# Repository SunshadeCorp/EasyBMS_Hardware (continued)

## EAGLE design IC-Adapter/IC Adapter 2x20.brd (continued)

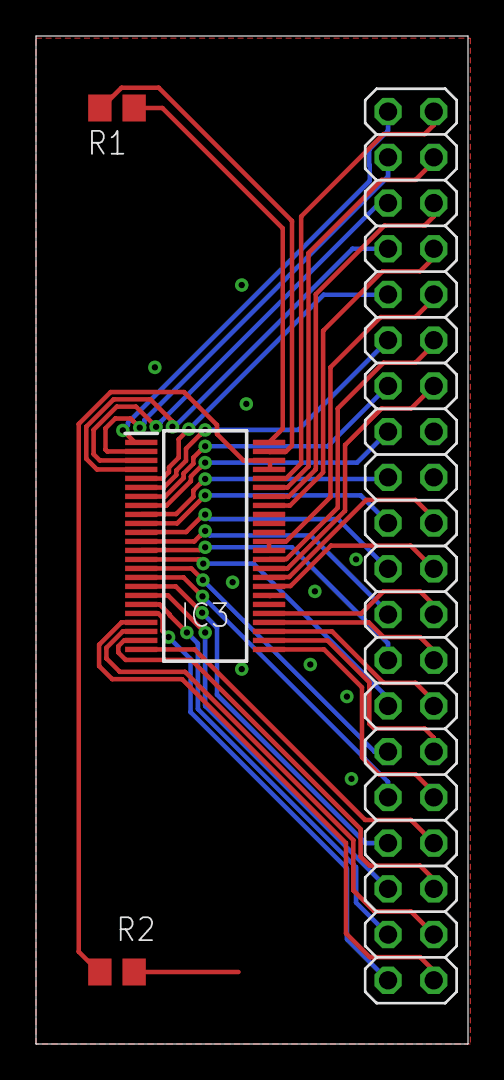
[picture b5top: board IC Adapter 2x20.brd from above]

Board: 2 copper layers, 24.0 x 56.0 mm, 4 parts (0 on the bottom side), 42 nets.

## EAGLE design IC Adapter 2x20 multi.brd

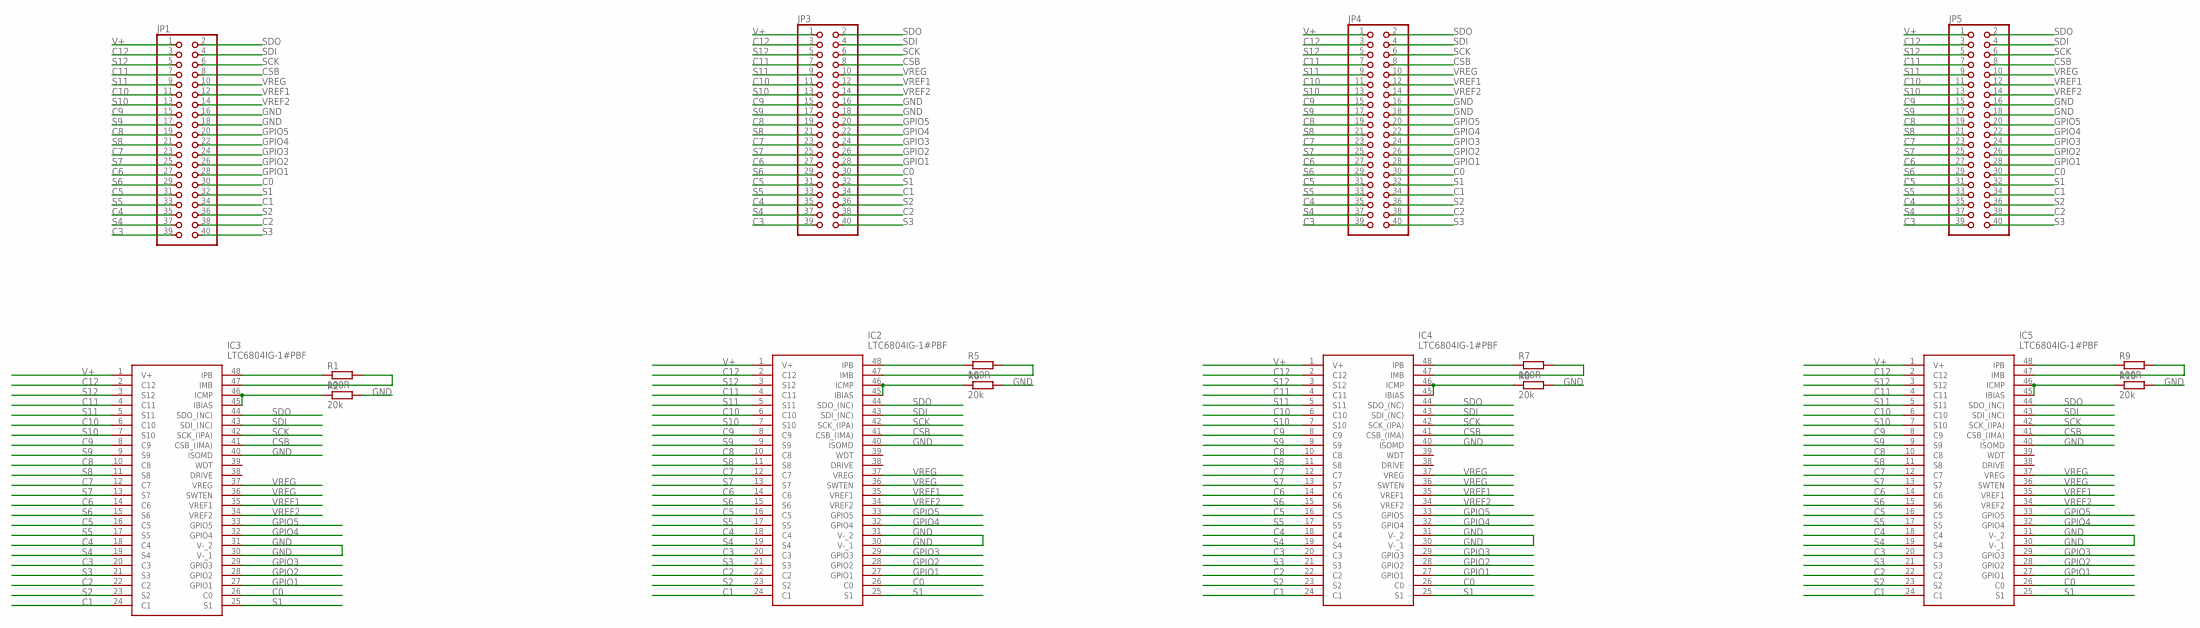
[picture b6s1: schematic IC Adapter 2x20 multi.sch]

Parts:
IC2, IC3, IC4, IC5: LTC6804IG-1#PBF; SOP50P780X200-48N
JP1, JP3, JP4, JP5: PINHD-2X20; 2X20
R1, R5, R7, R9: 100R; R0805
R2, R6, R8, R10: 20k; R0805

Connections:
C0: IC2.26 (C0), IC3.26 (C0), IC4.26 (C0), IC5.26 (C0), JP1.30, JP3.30, JP4.30, JP5.30
C1: IC2.24 (C1), IC3.24 (C1), IC4.24 (C1), IC5.24 (C1), JP1.34, JP3.34, JP4.34, JP5.34
C2: IC2.22 (C2), IC3.22 (C2), IC4.22 (C2), IC5.22 (C2), JP1.38, JP3.38, JP4.38, JP5.38
C3: IC2.20 (C3), IC3.20 (C3), IC4.20 (C3), IC5.20 (C3), JP1.39, JP3.39, JP4.39, JP5.39
C4: IC2.18 (C4), IC3.18 (C4), IC4.18 (C4), IC5.18 (C4), JP1.35, JP3.35, JP4.35, JP5.35
C5: IC2.16 (C5), IC3.16 (C5), IC4.16 (C5), IC5.16 (C5), JP1.31, JP3.31, JP4.31, JP5.31
C6: IC2.14 (C6), IC3.14 (C6), IC4.14 (C6), IC5.14 (C6), JP1.27, JP3.27, JP4.27, JP5.27
C7: IC2.12 (C7), IC3.12 (C7), IC4.12 (C7), IC5.12 (C7), JP1.23, JP3.23, JP4.23, JP5.23
C8: IC2.10 (C8), IC3.10 (C8), IC4.10 (C8), IC5.10 (C8), JP1.19, JP3.19, JP4.19, JP5.19
C9: IC2.8 (C9), IC3.8 (C9), IC4.8 (C9), IC5.8 (C9), JP1.15, JP3.15, JP4.15, JP5.15
C10: IC2.6 (C10), IC3.6 (C10), IC4.6 (C10), IC5.6 (C10), JP1.11, JP3.11, JP4.11, JP5.11
C11: IC2.4 (C11), IC3.4 (C11), IC4.4 (C11), IC5.4 (C11), JP1.7, JP3.7, JP4.7, JP5.7
C12: IC2.2 (C12), IC3.2 (C12), IC4.2 (C12), IC5.2 (C12), JP1.3, JP3.3, JP4.3, JP5.3
CSB: IC2.41 (CSB_(IMA)), IC3.41 (CSB_(IMA)), IC4.41 (CSB_(IMA)), IC5.41 (CSB_(IMA)), JP1.8, JP3.8, JP4.8, JP5.8
GND: IC2.30 (V-_1), IC2.31 (V-_2), IC2.40 (ISOMD), IC3.30 (V-_1), IC3.31 (V-_2), IC3.40 (ISOMD), IC4.30 (V-_1), IC4.31 (V-_2), IC4.40 (ISOMD), IC5.30 (V-_1), IC5.31 (V-_2), IC5.40 (ISOMD), JP1.16, JP1.18, JP3.16, JP3.18, JP4.16, JP4.18, JP5.16, JP5.18, R2.2, R6.2, R8.2, R10.2
GPIO1: IC2.27 (GPIO1), IC3.27 (GPIO1), IC4.27 (GPIO1), IC5.27 (GPIO1), JP1.28, JP3.28, JP4.28, JP5.28
GPIO2: IC2.28 (GPIO2), IC3.28 (GPIO2), IC4.28 (GPIO2), IC5.28 (GPIO2), JP1.26, JP3.26, JP4.26, JP5.26
GPIO3: IC2.29 (GPIO3), IC3.29 (GPIO3), IC4.29 (GPIO3), IC5.29 (GPIO3), JP1.24, JP3.24, JP4.24, JP5.24
GPIO4: IC2.32 (GPIO4), IC3.32 (GPIO4), IC4.32 (GPIO4), IC5.32 (GPIO4), JP1.22, JP3.22, JP4.22, JP5.22
GPIO5: IC2.33 (GPIO5), IC3.33 (GPIO5), IC4.33 (GPIO5), IC5.33 (GPIO5), JP1.20, JP3.20, JP4.20, JP5.20
ICMP: IC3.45 (IBIAS), IC3.46 (ICMP), R2.1
ICMP2: IC2.45 (IBIAS), IC2.46 (ICMP), R6.1
ICMP3: IC4.45 (IBIAS), IC4.46 (ICMP), R8.1
ICMP4: IC5.45 (IBIAS), IC5.46 (ICMP), R10.1
unnamed: IC3.48 (IPB), R1.1
unnamed: IC3.47 (IMB), R1.2
unnamed: IC2.48 (IPB), R5.1
unnamed: IC2.47 (IMB), R5.2
unnamed: IC4.48 (IPB), R7.1
unnamed: IC4.47 (IMB), R7.2
unnamed: IC5.48 (IPB), R9.1
unnamed: IC5.47 (IMB), R9.2
S1: IC2.25 (S1), IC3.25 (S1), IC4.25 (S1), IC5.25 (S1), JP1.32, JP3.32, JP4.32, JP5.32
S2: IC2.23 (S2), IC3.23 (S2), IC4.23 (S2), IC5.23 (S2), JP1.36, JP3.36, JP4.36, JP5.36
S3: IC2.21 (S3), IC3.21 (S3), IC4.21 (S3), IC5.21 (S3), JP1.40, JP3.40, JP4.40, JP5.40
S4: IC2.19 (S4), IC3.19 (S4), IC4.19 (S4), IC5.19 (S4), JP1.37, JP3.37, JP4.37, JP5.37
S5: IC2.17 (S5), IC3.17 (S5), IC4.17 (S5), IC5.17 (S5), JP1.33, JP3.33, JP4.33, JP5.33
S6: IC2.15 (S6), IC3.15 (S6), IC4.15 (S6), IC5.15 (S6), JP1.29, JP3.29, JP4.29, JP5.29
S7: IC2.13 (S7), IC3.13 (S7), IC4.13 (S7), IC5.13 (S7), JP1.25, JP3.25, JP4.25, JP5.25
S8: IC2.11 (S8), IC3.11 (S8), IC4.11 (S8), IC5.11 (S8), JP1.21, JP3.21, JP4.21, JP5.21
S9: IC2.9 (S9), IC3.9 (S9), IC4.9 (S9), IC5.9 (S9), JP1.17, JP3.17, JP4.17, JP5.17
S10: IC2.7 (S10), IC3.7 (S10), IC4.7 (S10), IC5.7 (S10), JP1.13, JP3.13, JP4.13, JP5.13
S11: IC2.5 (S11), IC3.5 (S11), IC4.5 (S11), IC5.5 (S11), JP1.9, JP3.9, JP4.9, JP5.9
S12: IC2.3 (S12), IC3.3 (S12), IC4.3 (S12), IC5.3 (S12), JP1.5, JP3.5, JP4.5, JP5.5
SCK: IC2.42 (SCK_(IPA)), IC3.42 (SCK_(IPA)), IC4.42 (SCK_(IPA)), IC5.42 (SCK_(IPA)), JP1.6, JP3.6, JP4.6, JP5.6
SDI: IC2.43 (SDI_(NC)), IC3.43 (SDI_(NC)), IC4.43 (SDI_(NC)), IC5.43 (SDI_(NC)), JP1.4, JP3.4, JP4.4, JP5.4
SDO: IC2.44 (SDO_(NC)), IC3.44 (SDO_(NC)), IC4.44 (SDO_(NC)), IC5.44 (SDO_(NC)), JP1.2, JP3.2, JP4.2, JP5.2
V+: IC2.1 (V+), IC3.1 (V+), IC4.1 (V+), IC5.1 (V+), JP1.1, JP3.1, JP4.1, JP5.1
VREF1: IC2.35 (VREF1), IC3.35 (VREF1), IC4.35 (VREF1), IC5.35 (VREF1), JP1.12, JP3.12, JP4.12, JP5.12
VREF2: IC2.34 (VREF2), IC3.34 (VREF2), IC4.34 (VREF2), IC5.34 (VREF2), JP1.14, JP3.14, JP4.14, JP5.14
VREG: IC2.36 (SWTEN), IC2.37 (VREG), IC3.36 (SWTEN), IC3.37 (VREG), IC4.36 (SWTEN), IC4.37 (VREG), IC5.36 (SWTEN), IC5.37 (VREG), JP1.10, JP3.10, JP4.10, JP5.10

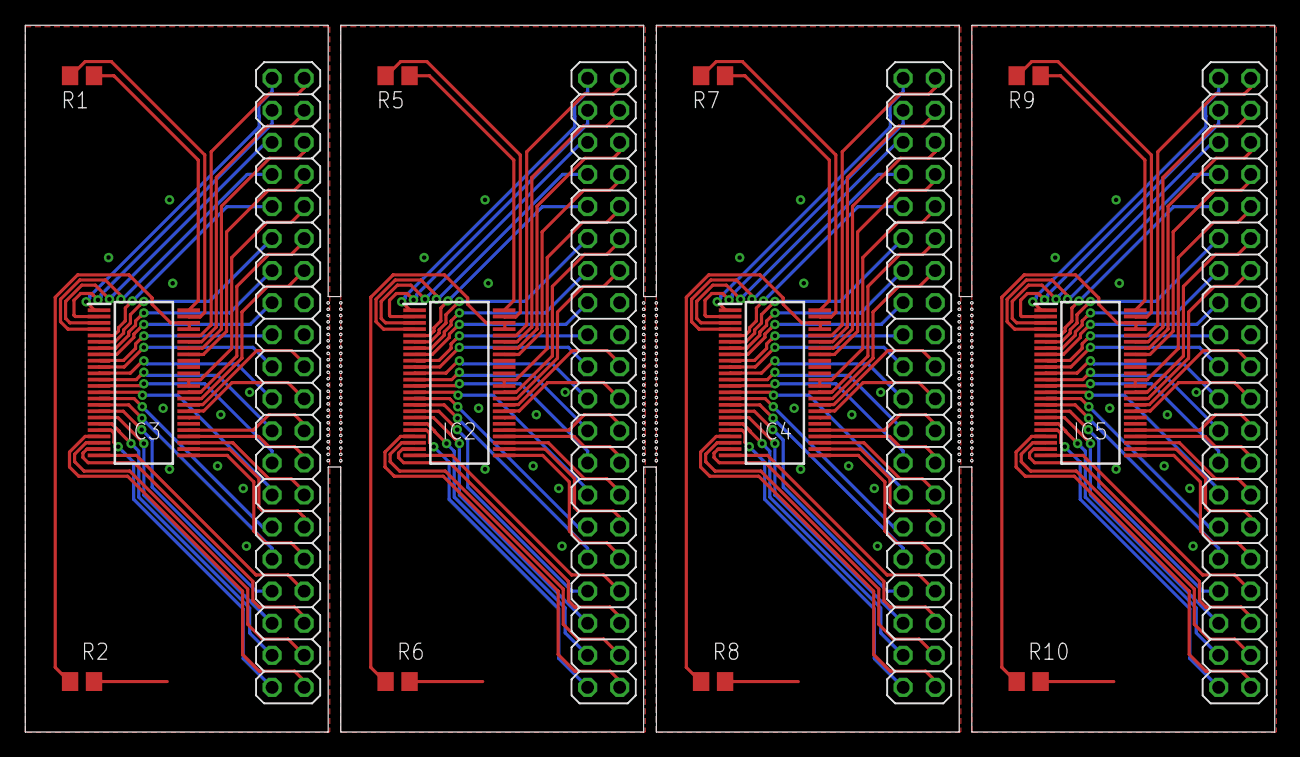
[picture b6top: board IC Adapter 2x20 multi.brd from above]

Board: 2 copper layers, 99.0 x 56.0 mm, 16 parts (0 on the bottom side), 51 nets.

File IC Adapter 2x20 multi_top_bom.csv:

Comment,Designator,Footprint,LCSC Part #
20k,R2 R6 R8,R0805,
100R,R1 R5 R7,R0805,
LTC6804IG-1#PBF,IC2 IC3 IC4,SOP50P780X200-48N,

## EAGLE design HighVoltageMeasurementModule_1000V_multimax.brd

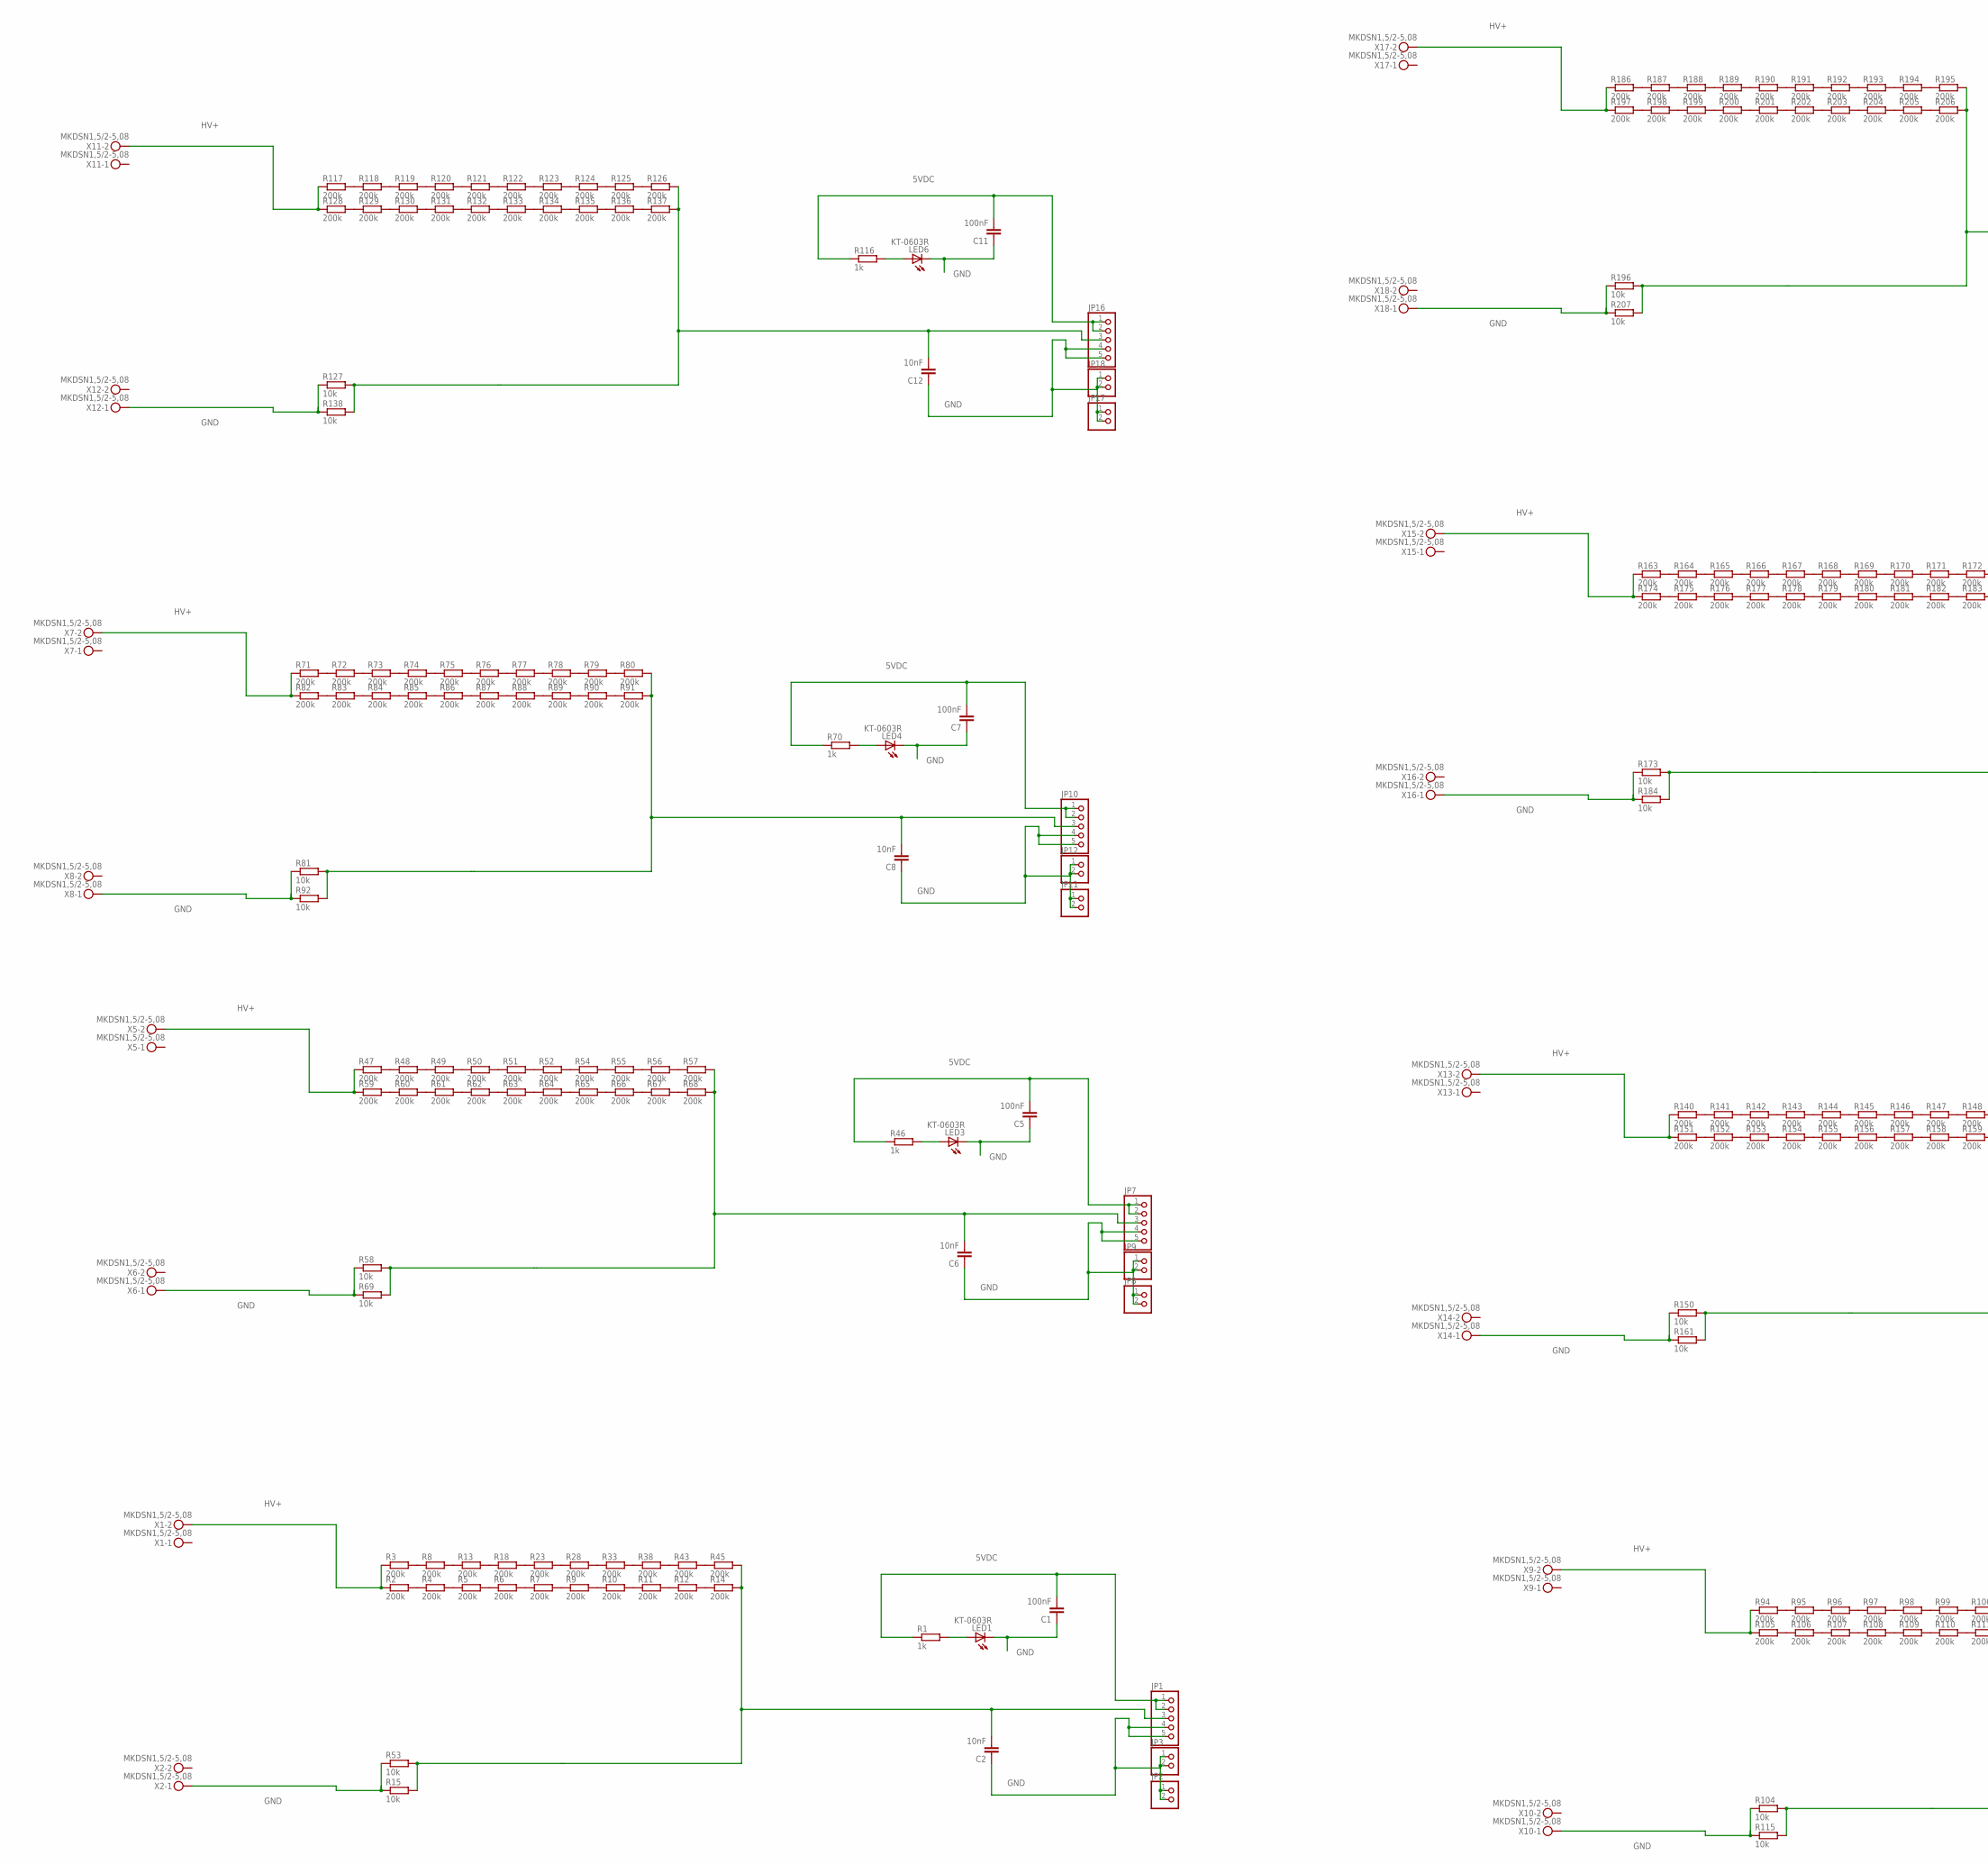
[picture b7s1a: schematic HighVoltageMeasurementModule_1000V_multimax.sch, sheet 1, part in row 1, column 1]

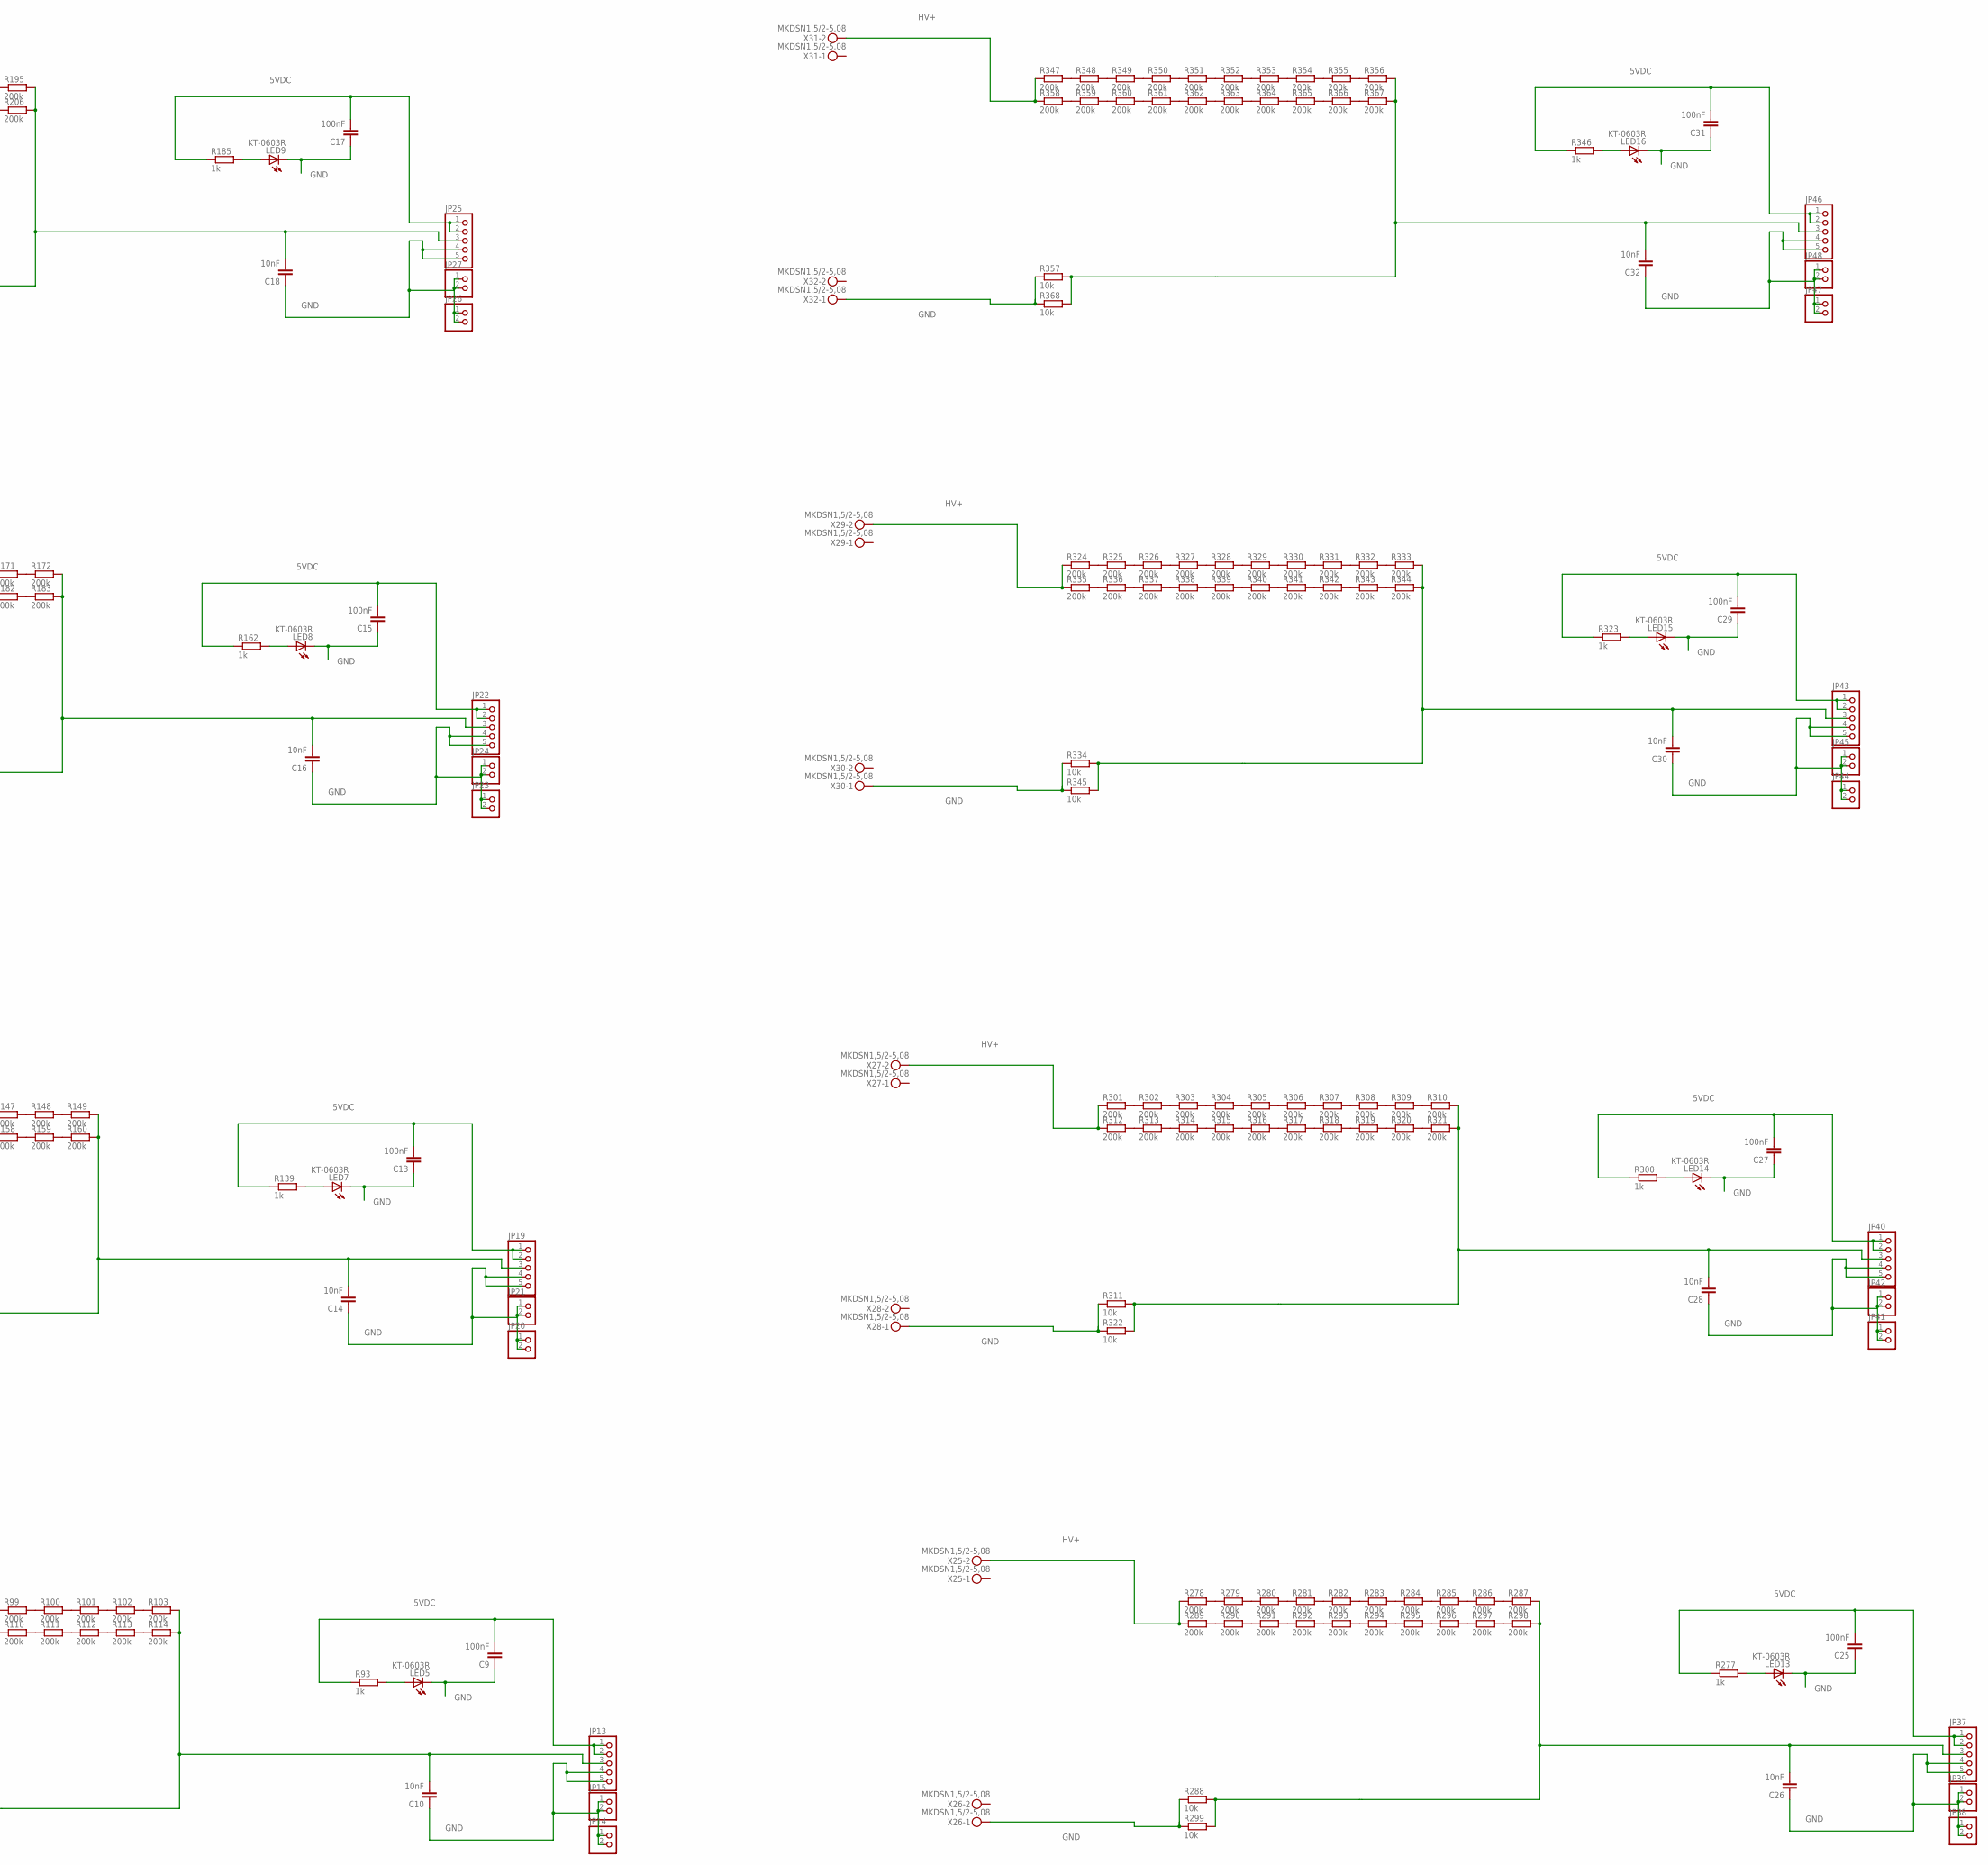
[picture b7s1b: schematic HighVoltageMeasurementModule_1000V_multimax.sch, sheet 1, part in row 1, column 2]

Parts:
C1, C5, C7, C9, C11, C13, C15, C17, C25, C27, C29, C31: 100nF; C0805
C2, C6, C8, C10, C12, C14, C16, C18, C26, C28, C30, C32: 10nF; C0805
JP1, JP7, JP10, JP13, JP16, JP19, JP22, JP25, JP37, JP40, JP43, JP46: PINHD-1X5; 1X05
JP2, JP3, JP8, JP9, JP11, JP12, JP14, JP15, JP17, JP18, JP20, JP21, JP23, JP24, JP26, JP27, JP38, JP39, JP41, JP42, JP44, JP45, JP47, JP48: PINHD-1X2; 1X02
LED1, LED3, LED4, LED5, LED6, LED7, LED8, LED9, LED13, LED14, LED15, LED16: KT-0603R; CHIPLED_0603
R1, R46, R70, R93, R116, R139, R162, R185, R277, R300, R323, R346: 1k; R0805
R2, R3, R4, R5, R6, R7, R8, R9, R10, R11, R12, R13, R14, R18, R23, R28, R33, R38, R43, R45, R47, R48, R49, R50, R51, R52, R54, R55, R56, R57, R59, R60, R61, R62, R63, R64, R65, R66, R67, R68, R71, R72, R73, R74, R75, R76, R77, R78, R79, R80, R82, R83, R84, R85, R86, R87, R88, R89, R90, R91, R94, R95, R96, R97, R98, R99, R100, R101, R102, R103, R105, R106, R107, R108, R109, R110, R111, R112, R113, R114, R117, R118, R119, R120, R121, R122, R123, R124, R125, R126, R128, R129, R130, R131, R132, R133, R134, R135, R136, R137, R140, R141, R142, R143, R144, R145, R146, R147, R148, R149, R151, R152, R153, R154, R155, R156, R157, R158, R159, R160, R163, R164, R165, R166, R167, R168, R169, R170, R171, R172, R174, R175, R176, R177, R178, R179, R180, R181, R182, R183, R186, R187, R188, R189, R190, R191, R192, R193, R194, R195, R197, R198, R199, R200, R201, R202, R203, R204, R205, R206, R278, R279, R280, R281, R282, R283, R284, R285, R286, R287, R289, R290, R291, R292, R293, R294, R295, R296, R297, R298, R301, R302, R303, R304, R305, R306, R307, R308, R309, R310, R312, R313, R314, R315, R316, R317, R318, R319, R320, R321, R324, R325, R326, R327, R328, R329, R330, R331, R332, R333, R335, R336, R337, R338, R339, R340, R341, R342, R343, R344, R347, R348, R349, R350, R351, R352, R353, R354, R355, R356, R358, R359, R360, R361, R362, R363, R364, R365, R366, R367: 200k; R0805
R15, R53, R58, R69, R81, R92, R104, R115, R127, R138, R150, R161, R173, R184, R196, R207, R288, R299, R311, R322, R334, R345, R357, R368: 10k; R0805
X1, X2, X5, X6, X7, X8, X9, X10, X11, X12, X13, X14, X15, X16, X17, X18, X25, X26, X27, X28, X29, X30, X31, X32: MKDSN1,5/2-5,08

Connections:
5VDC: C1.2, C5.2, C7.2, C9.2, C11.2, C13.2, C15.2, C17.2, C25.2, C27.2, C29.2, C31.2, JP1.1, JP1.2, JP7.1, JP7.2, JP10.1, JP10.2, JP13.1, JP13.2, JP16.1, JP16.2, JP19.1, JP19.2, JP22.1, JP22.2, JP25.1, JP25.2, JP37.1, JP37.2, JP40.1, JP40.2, JP43.1, JP43.2, JP46.1, JP46.2, R1.1, R46.1, R70.1, R93.1, R116.1, R139.1, R162.1, R185.1, R277.1, R300.1, R323.1, R346.1
GND: C1.1, C2.1, C5.1, C6.1, C7.1, C8.1, C9.1, C10.1, C11.1, C12.1, C13.1, C14.1, C15.1, C16.1, C17.1, C18.1, C25.1, C26.1, C27.1, C28.1, C29.1, C30.1, C31.1, C32.1, JP1.4, JP1.5, JP2.1, JP2.2, JP3.1, JP3.2, JP7.4, JP7.5, JP8.1, JP8.2, JP9.1, JP9.2, JP10.4, JP10.5, JP11.1, JP11.2, JP12.1, JP12.2, JP13.4, JP13.5, JP14.1, JP14.2, JP15.1, JP15.2, JP16.4, JP16.5, JP17.1, JP17.2, JP18.1, JP18.2, JP19.4, JP19.5, JP20.1, JP20.2, JP21.1, JP21.2, JP22.4, JP22.5, JP23.1, JP23.2, JP24.1, JP24.2, JP25.4, JP25.5, JP26.1, JP26.2, JP27.1, JP27.2, JP37.4, JP37.5, JP38.1, JP38.2, JP39.1, JP39.2, JP40.4, JP40.5, JP41.1, JP41.2, JP42.1, JP42.2, JP43.4, JP43.5, JP44.1, JP44.2, JP45.1, JP45.2, JP46.4, JP46.5, JP47.1, JP47.2, JP48.1, JP48.2, LED1.C, LED3.C, LED4.C, LED5.C, LED6.C, LED7.C, LED8.C, LED9.C, LED13.C, LED14.C, LED15.C, LED16.C, R15.1, R53.1, R58.1, R69.1, R81.1, R92.1, R104.1, R115.1, R127.1, R138.1, R150.1, R161.1, R173.1, R184.1, R196.1, R207.1, R288.1, R299.1, R311.1, R322.1, R334.1, R345.1, R357.1, R368.1, X2.1, X6.1, X8.1, X10.1, X12.1, X14.1, X16.1, X18.1, X26.1, X28.1, X30.1, X32.1
HV+: R2.1, R3.1, R47.1, R59.1, R71.1, R82.1, R94.1, R105.1, R117.1, R128.1, R140.1, R151.1, R163.1, R174.1, R186.1, R197.1, R278.1, R289.1, R301.1, R312.1, R324.1, R335.1, R347.1, R358.1, X1.2, X5.2, X7.2, X9.2, X11.2, X13.2, X15.2, X17.2, X25.2, X27.2, X29.2, X31.2
unnamed: R2.2, R4.1
unnamed: R4.2, R5.1
unnamed: R5.2, R6.1
unnamed: R6.2, R7.1
unnamed: LED1.A, R1.2
unnamed: R7.2, R9.1
unnamed: R3.2, R8.1
unnamed: R8.2, R13.1
unnamed: R9.2, R10.1
unnamed: R10.2, R11.1
unnamed: R11.2, R12.1
unnamed: R12.2, R14.1
unnamed: R13.2, R18.1
unnamed: C2.2, JP1.3, R14.2, R15.2, R45.2, R53.2
unnamed: R18.2, R23.1
unnamed: R23.2, R28.1
unnamed: R28.2, R33.1
unnamed: R33.2, R38.1
unnamed: R38.2, R43.1
unnamed: LED3.A, R46.2
unnamed: R43.2, R45.1
unnamed: R47.2, R48.1
unnamed: R48.2, R49.1
unnamed: R49.2, R50.1
unnamed: R50.2, R51.1
unnamed: R51.2, R52.1
unnamed: R52.2, R54.1
unnamed: R54.2, R55.1
unnamed: R55.2, R56.1
unnamed: R56.2, R57.1
unnamed: R59.2, R60.1
unnamed: R60.2, R61.1
unnamed: R61.2, R62.1
unnamed: R62.2, R63.1
unnamed: R63.2, R64.1
unnamed: R64.2, R65.1
unnamed: R65.2, R66.1
unnamed: R66.2, R67.1
unnamed: R67.2, R68.1
unnamed: C6.2, JP7.3, R57.2, R58.2, R68.2, R69.2
unnamed: LED4.A, R70.2
unnamed: R71.2, R72.1
unnamed: R72.2, R73.1
unnamed: R73.2, R74.1
unnamed: R74.2, R75.1
unnamed: R75.2, R76.1
unnamed: R76.2, R77.1
unnamed: R77.2, R78.1
unnamed: R78.2, R79.1
unnamed: R79.2, R80.1
unnamed: R82.2, R83.1
unnamed: R83.2, R84.1
unnamed: R84.2, R85.1
unnamed: R85.2, R86.1
unnamed: R86.2, R87.1
unnamed: R87.2, R88.1
unnamed: R88.2, R89.1
unnamed: R89.2, R90.1
unnamed: R90.2, R91.1
unnamed: C8.2, JP10.3, R80.2, R81.2, R91.2, R92.2
unnamed: LED5.A, R93.2
unnamed: R94.2, R95.1
unnamed: R95.2, R96.1
unnamed: R96.2, R97.1
unnamed: R97.2, R98.1
unnamed: R98.2, R99.1
unnamed: R99.2, R100.1
unnamed: R100.2, R101.1
unnamed: R101.2, R102.1
unnamed: R102.2, R103.1
unnamed: R105.2, R106.1
unnamed: R106.2, R107.1
unnamed: R107.2, R108.1
unnamed: R108.2, R109.1
unnamed: R109.2, R110.1
unnamed: R110.2, R111.1
unnamed: R111.2, R112.1
unnamed: R112.2, R113.1
unnamed: R113.2, R114.1
unnamed: C10.2, JP13.3, R103.2, R104.2, R114.2, R115.2
unnamed: LED6.A, R116.2
unnamed: R117.2, R118.1
unnamed: R118.2, R119.1
unnamed: R119.2, R120.1
unnamed: R120.2, R121.1
unnamed: R121.2, R122.1
unnamed: R122.2, R123.1
unnamed: R123.2, R124.1
unnamed: R124.2, R125.1
unnamed: R125.2, R126.1
unnamed: R128.2, R129.1
unnamed: R129.2, R130.1
unnamed: R130.2, R131.1
unnamed: R131.2, R132.1
unnamed: R132.2, R133.1
unnamed: R133.2, R134.1
unnamed: R134.2, R135.1
unnamed: R135.2, R136.1
unnamed: R136.2, R137.1
unnamed: C12.2, JP16.3, R126.2, R127.2, R137.2, R138.2
unnamed: LED7.A, R139.2
unnamed: R140.2, R141.1
unnamed: R141.2, R142.1
unnamed: R142.2, R143.1
unnamed: R143.2, R144.1
unnamed: R144.2, R145.1
unnamed: R145.2, R146.1
unnamed: R146.2, R147.1
unnamed: R147.2, R148.1
unnamed: R148.2, R149.1
unnamed: R151.2, R152.1
unnamed: R152.2, R153.1
unnamed: R153.2, R154.1
unnamed: R154.2, R155.1
unnamed: R155.2, R156.1
unnamed: R156.2, R157.1
unnamed: R157.2, R158.1
unnamed: R158.2, R159.1
unnamed: R159.2, R160.1
unnamed: C14.2, JP19.3, R149.2, R150.2, R160.2, R161.2
unnamed: LED8.A, R162.2
unnamed: R163.2, R164.1
unnamed: R164.2, R165.1
unnamed: R165.2, R166.1
unnamed: R166.2, R167.1
unnamed: R167.2, R168.1
unnamed: R168.2, R169.1
unnamed: R169.2, R170.1
unnamed: R170.2, R171.1
unnamed: R171.2, R172.1
unnamed: R174.2, R175.1
unnamed: R175.2, R176.1
unnamed: R176.2, R177.1
unnamed: R177.2, R178.1
unnamed: R178.2, R179.1
unnamed: R179.2, R180.1
unnamed: R180.2, R181.1
unnamed: R181.2, R182.1
unnamed: R182.2, R183.1
unnamed: C16.2, JP22.3, R172.2, R173.2, R183.2, R184.2
unnamed: LED9.A, R185.2
unnamed: R186.2, R187.1
unnamed: R187.2, R188.1
unnamed: R188.2, R189.1
unnamed: R189.2, R190.1
unnamed: R190.2, R191.1
unnamed: R191.2, R192.1
unnamed: R192.2, R193.1
unnamed: R193.2, R194.1
unnamed: R194.2, R195.1
unnamed: R197.2, R198.1
unnamed: R198.2, R199.1
unnamed: R199.2, R200.1
unnamed: R200.2, R201.1
unnamed: R201.2, R202.1
unnamed: R202.2, R203.1
unnamed: R203.2, R204.1
unnamed: R204.2, R205.1
unnamed: R205.2, R206.1
unnamed: C18.2, JP25.3, R195.2, R196.2, R206.2, R207.2
unnamed: LED13.A, R277.2
unnamed: R278.2, R279.1
unnamed: R279.2, R280.1
unnamed: R280.2, R281.1
unnamed: R281.2, R282.1
unnamed: R282.2, R283.1
unnamed: R283.2, R284.1
unnamed: R284.2, R285.1
unnamed: R285.2, R286.1
unnamed: R286.2, R287.1
unnamed: R289.2, R290.1
unnamed: R290.2, R291.1
unnamed: R291.2, R292.1
unnamed: R292.2, R293.1
unnamed: R293.2, R294.1
unnamed: R294.2, R295.1
unnamed: R295.2, R296.1
unnamed: R296.2, R297.1
unnamed: R297.2, R298.1
unnamed: C26.2, JP37.3, R287.2, R288.2, R298.2, R299.2
unnamed: LED14.A, R300.2
unnamed: R301.2, R302.1
unnamed: R302.2, R303.1
unnamed: R303.2, R304.1
unnamed: R304.2, R305.1
unnamed: R305.2, R306.1
unnamed: R306.2, R307.1
unnamed: R307.2, R308.1
unnamed: R308.2, R309.1
unnamed: R309.2, R310.1
unnamed: R312.2, R313.1
unnamed: R313.2, R314.1
unnamed: R314.2, R315.1
unnamed: R315.2, R316.1
unnamed: R316.2, R317.1
unnamed: R317.2, R318.1
unnamed: R318.2, R319.1
unnamed: R319.2, R320.1
unnamed: R320.2, R321.1
unnamed: C28.2, JP40.3, R310.2, R311.2, R321.2, R322.2
unnamed: LED15.A, R323.2
unnamed: R324.2, R325.1
unnamed: R325.2, R326.1
unnamed: R326.2, R327.1
unnamed: R327.2, R328.1
unnamed: R328.2, R329.1
unnamed: R329.2, R330.1
unnamed: R330.2, R331.1
unnamed: R331.2, R332.1
unnamed: R332.2, R333.1
unnamed: R335.2, R336.1
unnamed: R336.2, R337.1
unnamed: R337.2, R338.1
unnamed: R338.2, R339.1
unnamed: R339.2, R340.1
unnamed: R340.2, R341.1
unnamed: R341.2, R342.1
unnamed: R342.2, R343.1
unnamed: R343.2, R344.1
unnamed: C30.2, JP43.3, R333.2, R334.2, R344.2, R345.2
unnamed: LED16.A, R346.2
unnamed: R347.2, R348.1
unnamed: R348.2, R349.1
unnamed: R349.2, R350.1
unnamed: R350.2, R351.1
unnamed: R351.2, R352.1
unnamed: R352.2, R353.1
unnamed: R353.2, R354.1
unnamed: R354.2, R355.1
unnamed: R355.2, R356.1
unnamed: R358.2, R359.1
unnamed: R359.2, R360.1
unnamed: R360.2, R361.1
unnamed: R361.2, R362.1
unnamed: R362.2, R363.1
unnamed: R363.2, R364.1
unnamed: R364.2, R365.1
unnamed: R365.2, R366.1
unnamed: R366.2, R367.1
unnamed: C32.2, JP46.3, R356.2, R357.2, R367.2, R368.2

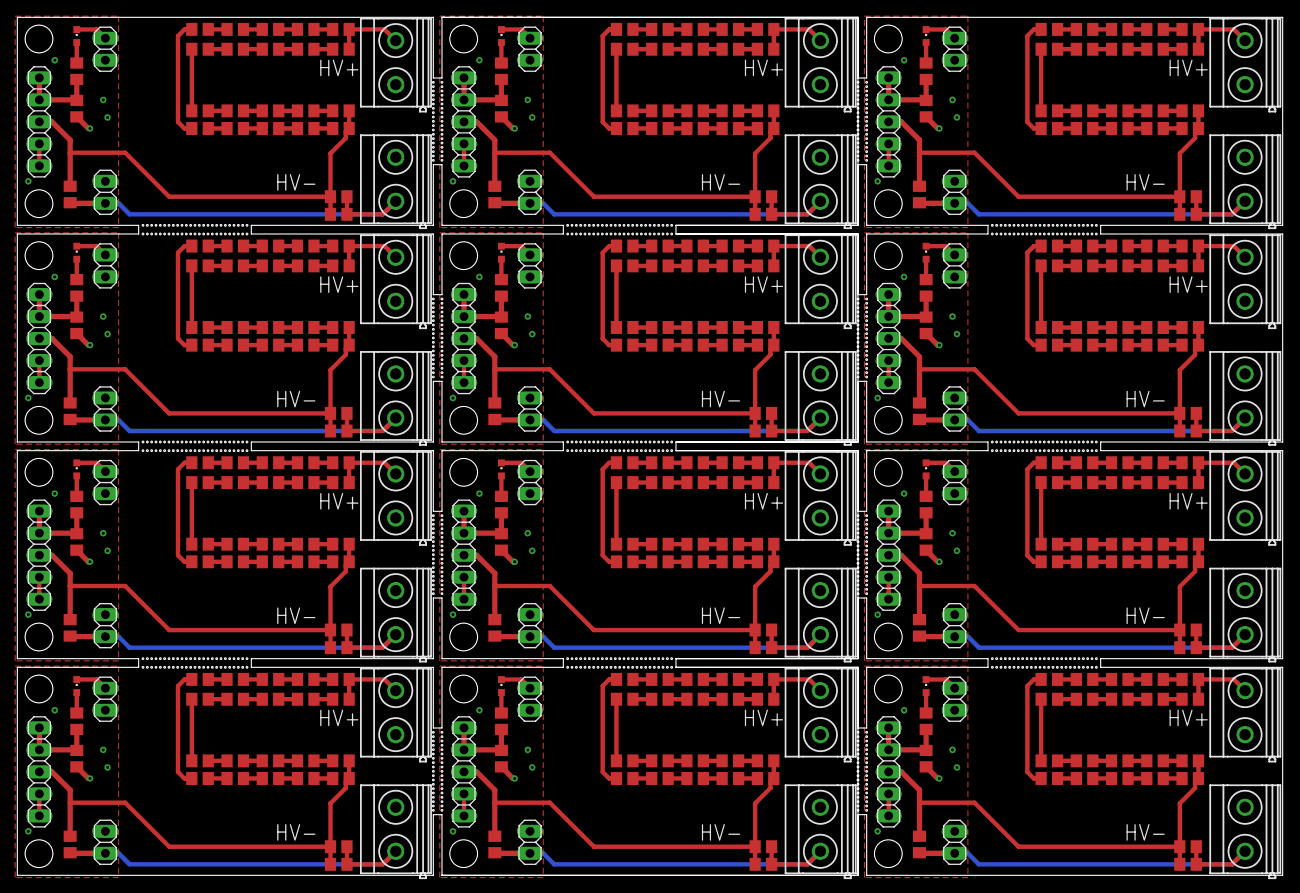
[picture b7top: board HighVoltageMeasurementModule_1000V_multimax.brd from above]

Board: 2 copper layers, 146.0 x 99.0 mm, 372 parts (0 on the bottom side), 243 nets.

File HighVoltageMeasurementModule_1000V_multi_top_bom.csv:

Comment,Designator,Footprint,LCSC Part #
1k,R1 R46 R70 R93 R116 R139 R162 R185,R0805,
10k,R15 R53 R58 R69 R81 R92 R104 R115 R127 R138 R150 R161 R173 R184 R196 R207,R0805,
10nF,C2 C6 C8 C10 C12 C14 C16 C18,C0805,
100nF,C1 C5 C7 C9 C11 C13 C15 C17,C0805,
200k,R2 R3 R4 R5 R6 R7 R8 R9 R10 R11 R12 R13 R14 R18 R23 R28 R33 R38 R43 R45 R47 R48 R49 R50 R51 R52 R54 R55 R56 R57 R59 R60 R61 R62 R63 R64 R65 R66 R67 R68 R71 R72 R73 R74 R75 R76 R77 R78 R79 R80 R82 R83 R84 R85 R86 R87 R88 R89 R90 R91 R94 R95 R96 R97 R98 R99 R100 R101 R102 R103 R105 R106 R107 R108 R109 R110 R111 R112 R113 R114 R117 R118 R119 R120 R121 R122 R123 R124 R125 R126 R128 R129 R130 R131 R132 R133 R134 R135 R136 R137 R140 R141 R142 R143 R144 R145 R146 R147 R148 R149 R151 R152 R153 R154 R155 R156 R157 R158 R159 R160 R163 R164 R165 R166 R167 R168 R169 R170 R171 R172 R174 R175 R176 R177 R178 R179 R180 R181 R182 R183 R186 R187 R188 R189 R190 R191 R192 R193 R194 R195 R197 R198 R199 R200 R201 R202 R203 R204 R205 R206,R0805,
KT-0603R,LED1 LED3 LED4 LED5 LED6 LED7 LED8 LED9,CHIPLED_0603,
